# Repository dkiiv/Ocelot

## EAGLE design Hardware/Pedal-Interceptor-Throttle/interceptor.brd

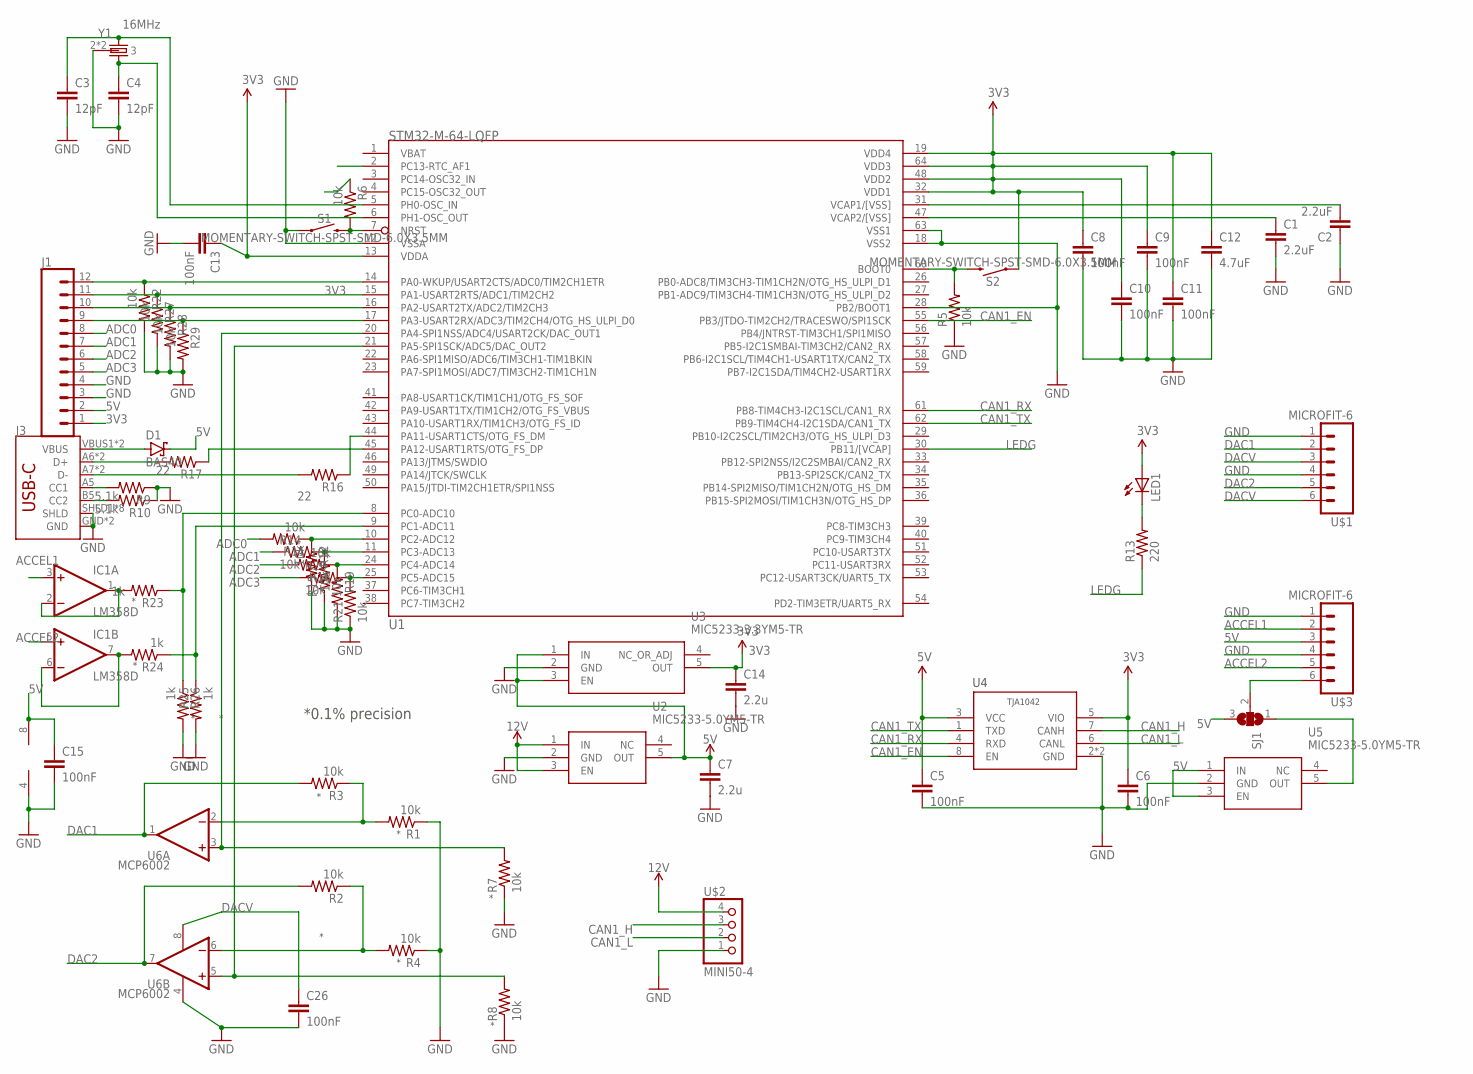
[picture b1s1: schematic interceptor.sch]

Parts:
C1, C2: 2.2uF; 0603-C
C3, C4: 12pF; 0603-C
C5, C6, C8, C9, C10, C11, C13, C15, C26: 100nF; 0603-C
C7, C14: 2.2u; C0603
C12: 4.7uF; 0603-C
D1: BAS40; SOT23
IC1: LM358D; SO08
J1: CONN_12; 1X12
J3: USB-C-BREAKOUT_SPARKFUN-CONNECTORS_USB_C16PIN; USB-C-BREAKOUT_SPARKFUN-CONNECTORS_USB-C-16P
LED1: LEDCHIPLED_0805; CHIPLED_0805
R1, R2, R3, R4, R5, R6, R7, R8, R11, R12, R14, R15, R18, R19, R20, R21, R22, R27, R28, R29: 10k; 0402-R
R9, R10: 5.1k; 0402-R
R13: 220; 0402-R
R16, R17: 22; 0402-R
R23, R24, R25, R26: 1k; 0402-R
S1, S2: MOMENTARY-SWITCH-SPST-SMD-6.0X3.5MM; TACTILE_SWITCH_SMD_6.0X3.5MM
SJ1: SJ2W; SJ_2
U1: STM32-M-64-LQFP; LQFP64
U2, U5: MIC5233-5.0YM5-TR; SOT95P280X145-5N
U3: MIC5233-3.3YM5-TR; SOT95P280X145-5N
U4: TJA1042HVSON; HVSON8
U6: MCP6002; SO08
U$1, U$3: MICROFIT-6
U$2: MINI50-4; MINI50
Y1: 16MHz; XTAL-3.2X2.5

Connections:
3V3: C6.1, C8.1, C9.1, C10.1, C11.1, C12.1, C13.1, C14.1, J1.1, LED1.A, R6.1, S2.1, U1.13 (VDDA), U1.19 (VDD4), U1.32 (VDD1), U1.48 (VDD2), U1.64 (VDD3), U3.5 (OUT), U4.5 (VIO)
5V: C5.1, C7.1, C15.1, D1.3 (C), IC1.8 (V+), J1.2, SJ1.3, U2.5 (OUT), U3.1 (IN), U3.3 (EN), U4.3 (VCC), U5.1 (IN), U5.3 (EN), U$3.3
12V: U2.1 (IN), U2.3 (EN), U$2.4 (1)
ACCEL1: IC1.3 (+IN), U$3.2
ACCEL2: IC1.5 (+IN), U$3.5
ADC0: J1.8, R11.2
ADC1: J1.7, R14.1
ADC2: J1.6, R18.2
ADC3: J1.5, R20.1
CAN1_EN: U1.55 (PB3/JTDO-TIM2CH2/TRACESWO/SPI1SCK), U4.8 (EN)
CAN1_H: U4.7 (CANH), U$2.3 (2)
CAN1_L: U4.6 (CANL), U$2.2 (3)
CAN1_RX: U1.61 (PB8-TIM4CH3-I2C1SCL/CAN1_RX), U4.4 (RXD)
CAN1_TX: U1.62 (PB9-TIM4CH4-I2C1SDA/CAN1_TX), U4.1 (TXD)
DAC1: R3.2, U6.1 (OUT), U$1.2
DAC2: R2.2, U6.7 (OUT), U$1.5
DACV: C26.1, U6.8 (V+), U$1.3, U$1.6
GND: C1.2, C2.1, C3.2, C4.2, C5.2, C6.2, C7.2, C8.2, C9.2, C10.2, C11.2, C12.2, C13.2, C14.2, C15.2, C26.2, IC1.4 (V-), J1.3, J1.4, J3.GND, J3.GND2 (GND), J3.SHLD1 (SHLD), J3.SHLD2 (SHLD), J3.SHLD3 (SHLD), J3.SHLD4 (SHLD), J3.SHLD5 (SHLD), J3.SHLD6 (SHLD), J3.SHLD7 (SHLD), J3.SHLD8 (SHLD), R1.1, R4.1, R5.1, R7.1, R8.1, R9.1, R10.1, R12.2, R15.1, R19.2, R21.1, R22.2, R25.2, R26.2, R27.2, R28.2, R29.2, S1.1, U1.12 (VSSA), U1.18 (VSS2), U1.28 (PB2/BOOT1), U1.63 (VSS1), U2.2 (GND), U3.2 (GND), U4.2 (GND), U4.PAD (GND), U5.2 (GND), U6.4 (V-), U$1.1, U$1.4, U$2.1 (4), U$3.1, U$3.4, Y1.2 (3), Y1.4 (3)
LEDG: R13.1, U1.30 (PB11/[VCAP])
unnamed: C3.1, U1.5 (PH0-OSC_IN), Y1.1
unnamed: R16.1, U1.44 (PA11-USART1CTS/OTG_FS_DM)
unnamed: C4.1, U1.6 (PH1-OSC_OUT), Y1.3 (2)
unnamed: R17.1, U1.45 (PA12-USART1RTS/OTG_FS_DP)
unnamed: J3.A7 (D-), J3.B7 (D-), R16.2
unnamed: J3.A6 (D+), J3.B6 (D+), R17.2
unnamed: R5.2, S2.2, U1.60 (BOOT0)
unnamed: J3.A5 (CC1), R9.2
unnamed: J3.B5 (CC2), R10.2
unnamed: R6.2, S1.2, U1.7 (NRST)
unnamed: D1.1 (A), J3.VBUS1 (VBUS), J3.VBUS2 (VBUS)
unnamed: SJ1.2, U$3.6
unnamed: IC1.1 (OUT), IC1.2 (-IN), R23.2
unnamed: SJ1.1, U5.5 (OUT)
unnamed: IC1.6 (-IN), IC1.7 (OUT), R24.2
unnamed: R11.1, R12.1, U1.10 (PC2-ADC12)
unnamed: R7.2, U1.20 (PA4-SPI1NSS/ADC4/USART2CK/DAC_OUT1), U6.3 (+IN)
unnamed: R8.2, U1.21 (PA5-SPI1SCK/ADC5/DAC_OUT2), U6.5 (+IN)
unnamed: R14.2, R15.2, U1.11 (PC3-ADC13)
unnamed: R18.1, R19.1, U1.24 (PC4-ADC14)
unnamed: R1.2, R3.1, U6.2 (-IN)
unnamed: R2.1, R4.2, U6.6 (-IN)
unnamed: R20.2, R21.2, U1.25 (PC5-ADC15)
unnamed: LED1.C, R13.2
unnamed: J1.9, R29.1, U1.17 (PA3-USART2RX/ADC3/TIM2CH4/OTG_HS_ULPI_D0)
unnamed: J1.10, R28.1, U1.16 (PA2-USART2TX/ADC2/TIM2CH3)
unnamed: J1.11, R27.1, U1.15 (PA1-USART2RTS/ADC1/TIM2CH2)
unnamed: J1.12, R22.1, U1.14 (PA0-WKUP/USART2CTS/ADC0/TIM2CH1ETR)
unnamed: R23.1, R26.1, U1.8 (PC0-ADC10)
unnamed: R24.1, R25.1, U1.9 (PC1-ADC11)
VCAP1: C2.2, U1.31 (VCAP1/[VSS])
VCAP2: C1.1, U1.47 (VCAP2/[VSS])

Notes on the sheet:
*0.1% precision

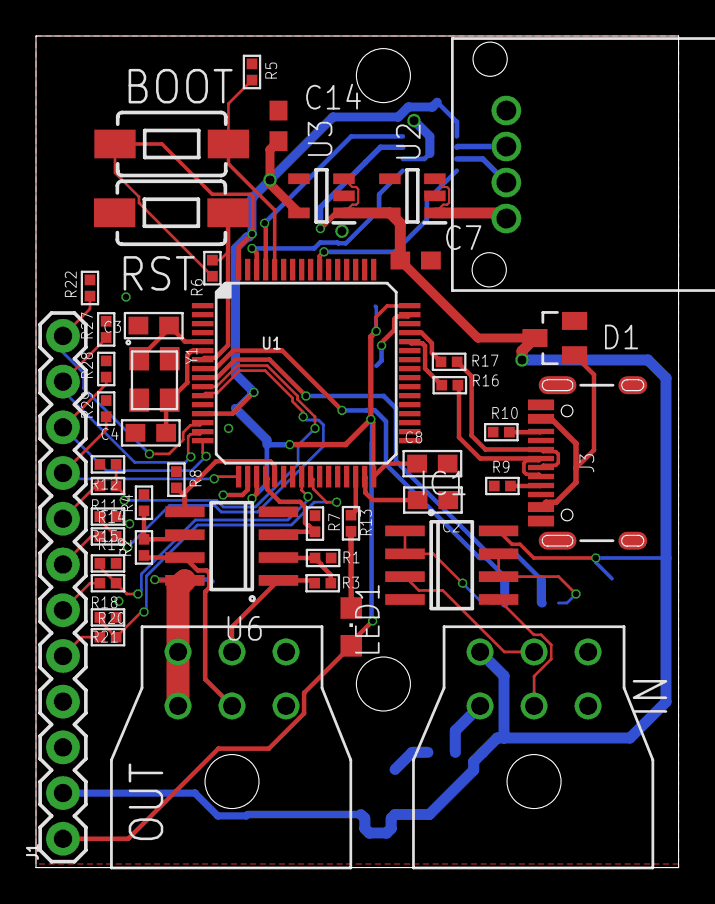
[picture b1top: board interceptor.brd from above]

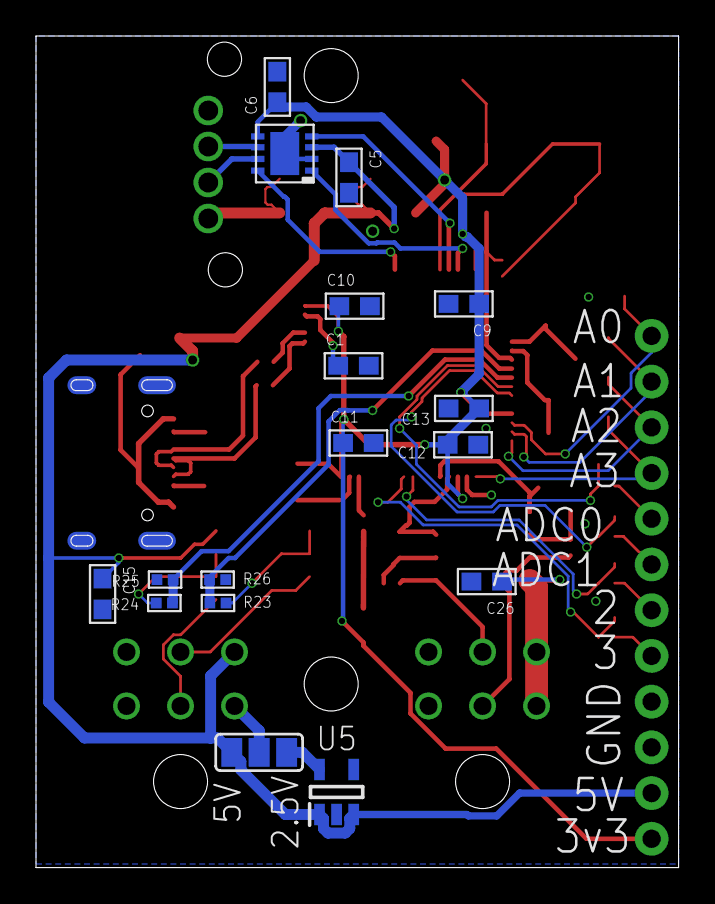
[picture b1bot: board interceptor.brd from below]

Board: 2 copper layers, 35.7 x 46.2 mm, 63 parts (17 on the bottom side), 51 nets.

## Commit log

2025-08-07 pq pla; try spoofing less signals to the EPS * if this works, set this WSS to static 0 and observe behavior
2025-08-08 pq pla; set another WSS to 0, optimize conditionals with HCA status
2026-03-09 init tesla_bench commit
2026-03-09 brrrrrrr * add tesla vehicle CAN messages * random data, some counters and crc

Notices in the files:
parts and their libraries:
SparkFun-Switches: Licensing: Creative Commons ShareAlike 4.0 International - https://creativecommons.org/licenses/by-sa/4.0
